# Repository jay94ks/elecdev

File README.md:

# Custom Development Board Projects.
This project is for making custom development boards with minimal circuits to power MCUs, including programming them.

## MISC
* USB-C breakout: https://github.com/jay94ks/elecdev/tree/main/misc/USB_C_BREAKOUT

## Raspberry-Pi Silicon
### RP2040
See this directory: https://github.com/jay94ks/elecdev/tree/main/rp2040 <br />
ARM® Cortex®-M0+ Dual-core, 32bit, QFN-56.<br />
Features: 133 MHz max, 256kB SRAM, `UART` x2, `SPI` x2, `I2C` x2, `PWM` x 16 channel.<br/>

### TODO: RP2350A, RP2354A 
### TODO: RP2350B, RP2354B
I'm waiting for these chips are available on chip stores. :)

## STM32
I love STMicroelectronics's `TSSOP-20` and `TSOP-8` (G03xJ6Mx).
It is small, has few pins, is easy to use by plugging it into a breadboard,
and has a simple peripheral circuit. I even like the size of the flash memory and the size of the built-in RAM. 
Additionally, they fit well on any board that can be made easily, and there is little need to configure an external clock circuit.
I hope more chips will be released in `TSSOP-20`, `TSSOP-16` or `TSOP-8` versions. And it would be better if they could have USB DP/DM pins.

### G030F6
See this directory: https://github.com/jay94ks/elecdev/tree/main/stm32/g030f6 <br />
ARM® Cortex®-M0, 32bit, TSOC-20.<br />
Features: 64 MHz MAX, 32K Flash, 8K RAM, `USART`, `SPI`,  `I2C`.<br/>
Board Size: 17.78 mm * 25.4 mm.<br />
Price: about 2,800 KRW, 2.11 USD.<br/>

### F042F6
See this directory: https://github.com/jay94ks/elecdev/tree/main/stm32/f042f6 <br />
ARM® Cortex®-M0, 32bit, TSOC-20.<br />
Features: 48 MHz MAX, 32K Flash, 6K RAM, `USART`, `SPI`, `USB FS`, `CAN`, `I2C`.<br/>
Board Size: 22.86 mm * 32.05 mm.<br />
Price: about 5,500 KRW, 4.15 USD.<br/>

### F107RBT6
See this directory: https://github.com/jay94ks/elecdev/tree/main/stm32/f107rbt6 <br />

### G030K8
See this directory: https://github.com/jay94ks/elecdev/tree/main/stm32/g030k8 <br />

## WCH
### CH32V003F4P6
See this directory: https://github.com/jay94ks/elecdev/tree/main/wch/ch32v003f4p6 <br />

### CH32V003F4U6
See this directory: https://github.com/jay94ks/elecdev/tree/main/wch/ch32v003f4u6 <br />

### CH32X033F6P6
TODO: I bought this chip few weeks ago, I'll design this one soon. (100 pcs)

### CH32X035G8U6
See this directory:  https://github.com/jay94ks/elecdev/tree/main/wch/ch32x035g8u6 <br />

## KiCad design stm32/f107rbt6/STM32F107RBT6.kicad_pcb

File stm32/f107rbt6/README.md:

## STM32F107RBT6
This custom board contains: LAN8720A, PoE support.

### Enable Ethernet on Connectivity.
Configure `Parameter Settings`(`ETH` in `Connectivity` page) like:

* Mode: `RMII`.
* Ethernet Media Configuration: as your wish.
* Ethernet MAC Address: set anything except `00:00:00:00:00:00`.
* PHY Address Value: `0` (this is important!)

And then, enable `LWIP` to test the board's ethernet operational:
(This is located at `Middleware`)
* Check `Enabled` on `LWIP`.
* `LWIP_ICMP` on `General Settings`: Enabled. <-- `ping` command is based on `ICMP` traffic.
* `MEM_SIZE` on `Key Options`: `10 * 1600`. (Optional)

### Pin Mapping.
To enable this chip functionality, configure `RMII`:

* RCC: 8MHz.
* PC1: ETH_MDC
* PA1: ETH_REF_CLK
* PA2: ETH_MDIO
* PA7: ETH_CRS_DV
* PC4: ETH_RXD0
* PC5: ETH_RXD1
* PB10: ETH_RX_ER
* PB11: ETH_TX_EN
* PB12: ETH_TXD0
* PB13: ETH_TXD1
* PA11: USB_OTG_FS_DM
* PA12: USB_OTG_FS_DP

### LAN8720A.
STM32CubeIDE supports only `LAN8742A` but, `LAN8720A` is available with few changes.
Configure `Advanced Parameters`(`ETH` in `Connectivity` page) like:

* PHY: `LAN8742A_PHY_ADDRESS`
* Transceiver Basic Control Register: `0x00`
* Transceiver Basic Status Register: `0x01`
* PHY special control/status register Offset: `0x1f`
* PHY interrupt source flag register Offset: `0x001d`
* PHY Link down interrupt: `0x0010`

When if `PHY Address Value` is not editable even though this changed on `Parameter Settings`,
This can be modified by header file: `stm32f1xx_hal_conf.h` on `Core/Inc` directory.

```
......
/* Section 2: PHY configuration section */

/* LAN8742A_PHY_ADDRESS Address*/
// #define LAN8742A_PHY_ADDRESS         0x1U    // <-- comment this.
#define LAN8742A_PHY_ADDRESS            0x0U    // <-- set `PHY_ADDRESS` here

......
```

Then, you can program the board supports `10/100 Mbps Ethernet`.

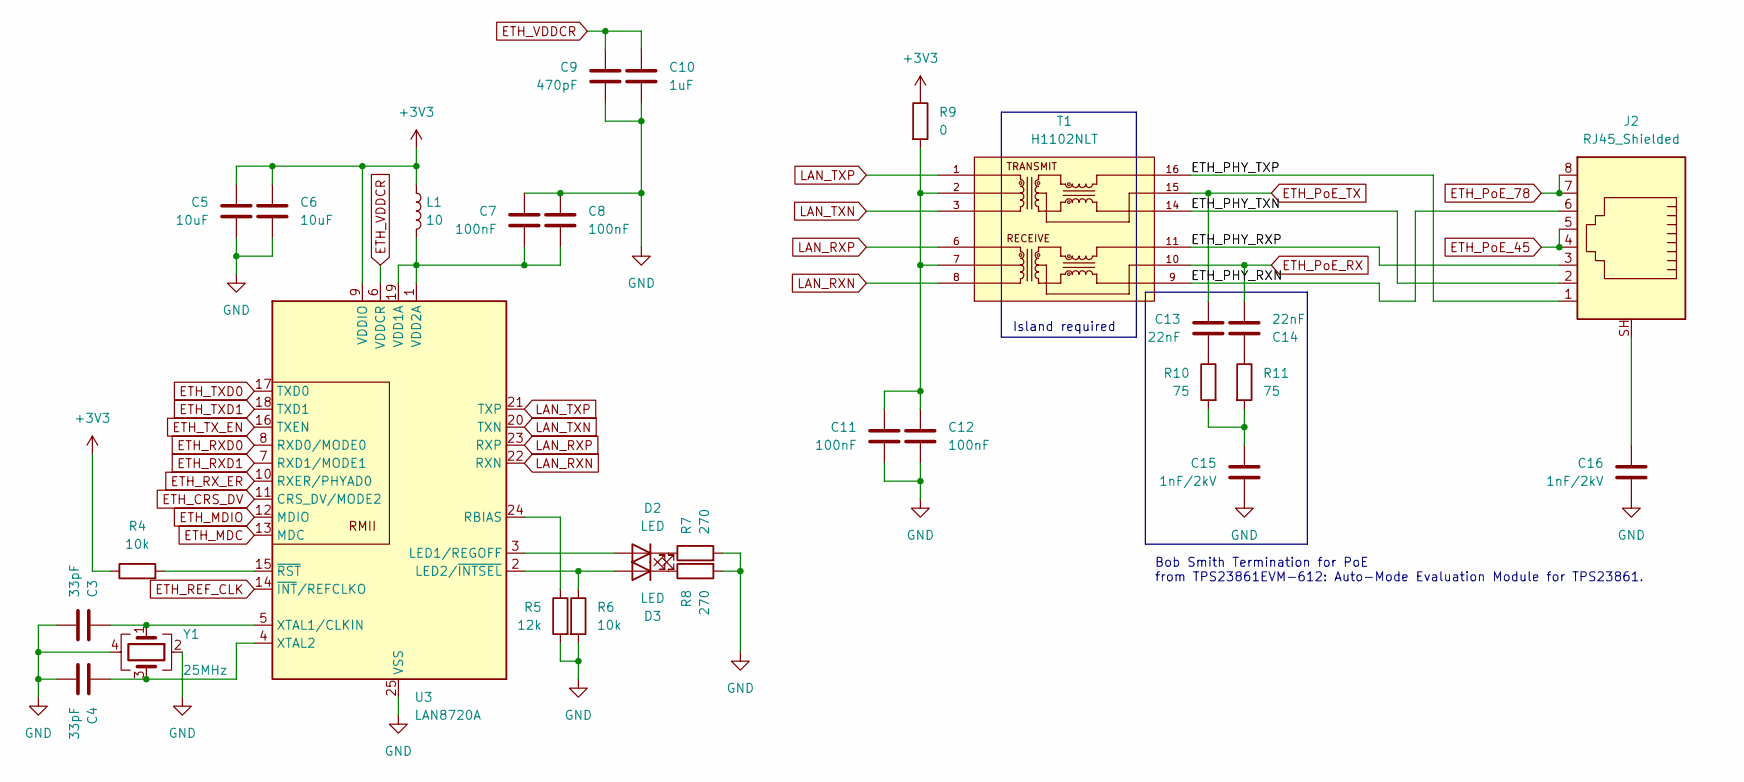
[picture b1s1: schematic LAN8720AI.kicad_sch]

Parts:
C3, C4: 33pF; C_0603_1608Metric
C5, C6: 10uF; C_0603_1608Metric
C7, C8, C11, C12: 100nF; C_0603_1608Metric
C9: 470pF; C_0603_1608Metric
C10: 1uF; C_0603_1608Metric
C13, C14: 22nF; C_0603_1608Metric
C15, C16: 1nF/2kV; C_0603_1608Metric
D2, D3: LED; LED_0603_1608Metric
J2: RJ45_Shielded; RJ45_Ninigi_GE
L1: 10; L_0603_1608Metric
R4, R6: 10k; R_0603_1608Metric
R5: 12k; R_0603_1608Metric
R7, R8: 270; R_0603_1608Metric
R9: 0; R_0603_1608Metric
R10, R11: 75; R_0603_1608Metric
T1: H1102NLT; XFMR_H1102NLT; PARTREV NA
U3: LAN8720A; VQFN-24-1EP_4x4mm_P0.5mm_EP2.45x2.45mm
Y1: 25MHz; Crystal_SMD_3225-4Pin_3.2x2.5mm

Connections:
+3V3: C5.1, C6.1, L1.1, R4.1, R9.1, U3.9 (VDDIO); also elsewhere on the board
/LAN8720AI/ETH_PHY_RXN: J2.6, T1.9
/LAN8720AI/ETH_PHY_RXP: J2.3, T1.11
/LAN8720AI/ETH_PHY_TXN: J2.2, T1.14
/LAN8720AI/ETH_PHY_TXP: J2.1, T1.16
ETH_CRS_DV: U3.11 (CRS_DV/MODE2); also elsewhere on the board
ETH_MDC: U3.13 (MDC); also elsewhere on the board
ETH_MDIO: U3.12 (MDIO); also elsewhere on the board
ETH_PoE_45: J2.4, J2.5; also elsewhere on the board
ETH_PoE_78: J2.7, J2.8; also elsewhere on the board
ETH_PoE_RX: C14.2, T1.10; also elsewhere on the board
ETH_PoE_TX: C13.1, T1.15; also elsewhere on the board
ETH_REF_CLK: U3.14 (~INT/REFCLKO); also elsewhere on the board
ETH_RXD0: U3.8 (RXD0/MODE0); also elsewhere on the board
ETH_RXD1: U3.7 (RXD1/MODE1); also elsewhere on the board
ETH_RX_ER: U3.10 (RXER/PHYAD0); also elsewhere on the board
ETH_TXD0: U3.17 (TXD0); also elsewhere on the board
ETH_TXD1: U3.18 (TXD1); also elsewhere on the board
ETH_TX_EN: U3.16 (TXEN); also elsewhere on the board
ETH_VDDCR: C9.1, C10.1, U3.6 (VDDCR)
GND: C3.2, C4.2, C5.2, C6.2, C7.1, C8.1, C9.2, C10.2, C11.2, C12.2, C15.2, C16.2, R5.2, R6.2, R7.2, R8.2, U3.25 (VSS), Y1.2, Y1.4; also elsewhere on the board
LAN_RXN: T1.8, U3.22 (RXN)
LAN_RXP: T1.6, U3.23 (RXP)
LAN_TXN: T1.3, U3.20 (TXN)
LAN_TXP: T1.1, U3.21 (TXP)
unnamed: C11.1, C12.1, R9.2, T1.2, T1.7
unnamed: C13.2, R10.1
unnamed: C14.1, R11.1
unnamed: C15.1, R10.2, R11.2
unnamed: C16.1, J2.SH
unnamed: D2.2 (A), U3.3 (LED1/REGOFF)
unnamed: D2.1 (K), R7.1
unnamed: D3.2 (A), R6.1, U3.2 (LED2/~INTSEL)
unnamed: D3.1 (K), R8.1
unnamed: R5.1, U3.24 (RBIAS)
unnamed: C7.2, C8.2, L1.2, U3.1 (VDD2A), U3.19 (VDD1A)
unnamed: C3.1, U3.5 (XTAL1/CLKIN), Y1.1
unnamed: C4.1, U3.4 (XTAL2), Y1.3
unnamed: R4.2, U3.15 (~RST)

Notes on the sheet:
Bob Smith Termination for PoE from TPS23861EVM-612: Auto-Mode Evaluation Module for TPS23861.
Island required

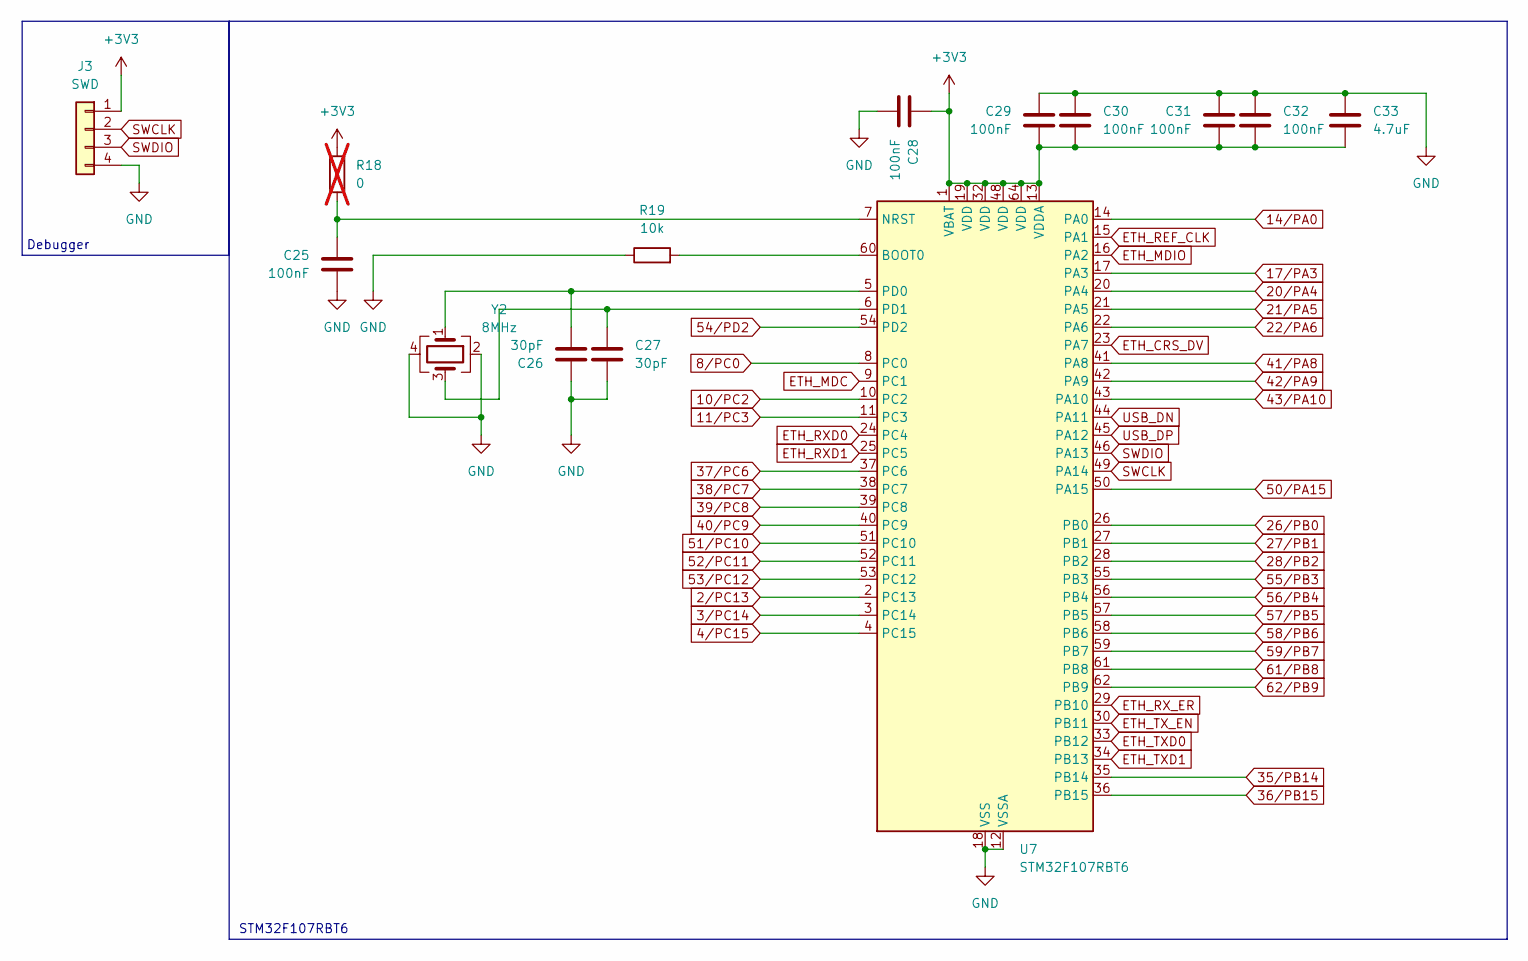
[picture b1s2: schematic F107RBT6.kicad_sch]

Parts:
C25, C28, C29, C30, C31, C32: 100nF; C_0603_1608Metric
C26, C27: 30pF; C_0603_1608Metric
C33: 4.7uF; C_0603_1608Metric
J3: SWD; PinHeader_1x04_P2.54mm_Vertical
R18: 0; R_0603_1608Metric; not fitted
R19: 10k; R_0603_1608Metric
U7: STM32F107RBT6; LQFP-64_10x10mm_P0.5mm
Y2: 8MHz; Crystal_SMD_3225-4Pin_3.2x2.5mm

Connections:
2/PC13: U7.2 (PC13); also elsewhere on the board
3/PC14: U7.3 (PC14); also elsewhere on the board
4/PC15: U7.4 (PC15); also elsewhere on the board
8/PC0: U7.8 (PC0); also elsewhere on the board
10/PC2: U7.10 (PC2); also elsewhere on the board
11/PC3: U7.11 (PC3); also elsewhere on the board
14/PA0: U7.14 (PA0); also elsewhere on the board
17/PA3: U7.17 (PA3); also elsewhere on the board
20/PA4: U7.20 (PA4); also elsewhere on the board
21/PA5: U7.21 (PA5); also elsewhere on the board
22/PA6: U7.22 (PA6); also elsewhere on the board
26/PB0: U7.26 (PB0); also elsewhere on the board
27/PB1: U7.27 (PB1); also elsewhere on the board
28/PB2: U7.28 (PB2); also elsewhere on the board
35/PB14: U7.35 (PB14); also elsewhere on the board
36/PB15: U7.36 (PB15); also elsewhere on the board
37/PC6: U7.37 (PC6); also elsewhere on the board
38/PC7: U7.38 (PC7); also elsewhere on the board
39/PC8: U7.39 (PC8); also elsewhere on the board
40/PC9: U7.40 (PC9); also elsewhere on the board
41/PA8: U7.41 (PA8); also elsewhere on the board
42/PA9: U7.42 (PA9); also elsewhere on the board
43/PA10: U7.43 (PA10); also elsewhere on the board
50/PA15: U7.50 (PA15); also elsewhere on the board
51/PC10: U7.51 (PC10); also elsewhere on the board
52/PC11: U7.52 (PC11); also elsewhere on the board
53/PC12: U7.53 (PC12); also elsewhere on the board
54/PD2: U7.54 (PD2); also elsewhere on the board
55/PB3: U7.55 (PB3); also elsewhere on the board
56/PB4: U7.56 (PB4); also elsewhere on the board
57/PB5: U7.57 (PB5); also elsewhere on the board
58/PB6: U7.58 (PB6); also elsewhere on the board
59/PB7: U7.59 (PB7); also elsewhere on the board
61/PB8: U7.61 (PB8); also elsewhere on the board
62/PB9: U7.62 (PB9); also elsewhere on the board
+3V3: C28.1, C29.2, C30.2, C31.2, C32.2, C33.2, J3.1, R18.1, U7.1 (VBAT), U7.13 (VDDA), U7.19 (VDD), U7.32 (VDD), U7.48 (VDD), U7.64 (VDD); also elsewhere on the board
ETH_CRS_DV: U7.23 (PA7); also elsewhere on the board
ETH_MDC: U7.9 (PC1); also elsewhere on the board
ETH_MDIO: U7.16 (PA2); also elsewhere on the board
ETH_REF_CLK: U7.15 (PA1); also elsewhere on the board
ETH_RXD0: U7.24 (PC4); also elsewhere on the board
ETH_RXD1: U7.25 (PC5); also elsewhere on the board
ETH_RX_ER: U7.29 (PB10); also elsewhere on the board
ETH_TXD0: U7.33 (PB12); also elsewhere on the board
ETH_TXD1: U7.34 (PB13); also elsewhere on the board
ETH_TX_EN: U7.30 (PB11); also elsewhere on the board
GND: C25.2, C26.1, C27.2, C28.2, C29.1, C30.1, C31.1, C32.1, C33.1, J3.4, R19.1, U7.12 (VSSA), U7.18 (VSS), U7.31 (VSS), U7.47 (VSS), U7.63 (VSS), Y2.2, Y2.4; also elsewhere on the board
unnamed: R19.2, U7.60 (BOOT0)
unnamed: C25.1, R18.2, U7.7 (NRST)
unnamed: C26.2, U7.5 (PD0), Y2.1
unnamed: C27.1, U7.6 (PD1), Y2.3
SWCLK: J3.2, U7.49 (PA14)
SWDIO: J3.3, U7.46 (PA13)
USB_DN: U7.44 (PA11); also elsewhere on the board
USB_DP: U7.45 (PA12); also elsewhere on the board

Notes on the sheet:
STM32F107RBT6
Debugger

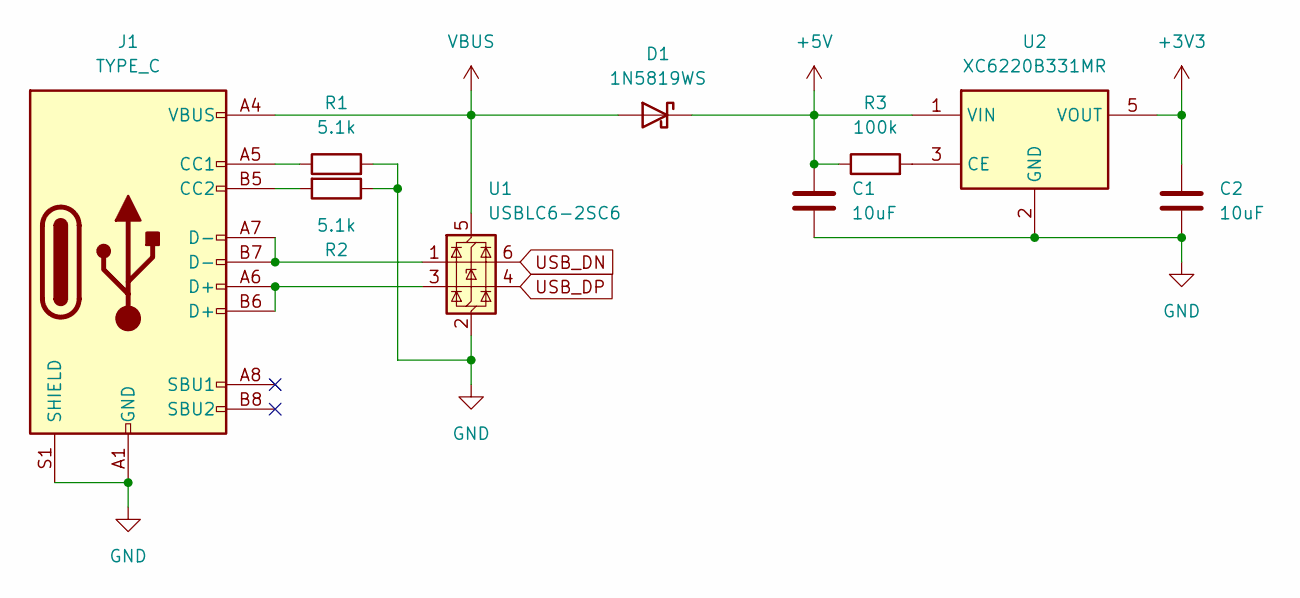
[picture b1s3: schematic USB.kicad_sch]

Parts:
C1, C2: 10uF; C_0603_1608Metric
D1: 1N5819WS; D_SOD-323
J1: TYPE_C; USB_C_Receptacle_Palconn_UTC16-G
R1, R2: 5.1k; R_0603_1608Metric
R3: 100k; R_0603_1608Metric
U1: USBLC6-2SC6; SOT-23-6
U2: XC6220B331MR; SOT-23-5

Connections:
+3V3: C2.1, U2.5 (VOUT); also elsewhere on the board
+5V: C1.1, D1.1 (K), R3.1, U2.1 (VIN); also elsewhere on the board
GND: C1.2, C2.2, J1.A1 (GND), J1.A12 (GND), J1.B1 (GND), J1.B12 (GND), J1.S1 (SHIELD), R1.2, R2.1, U1.2 (GND), U2.2 (GND); also elsewhere on the board
unnamed: J1.A5 (CC1), R1.1
unnamed: J1.B5 (CC2), R2.2
unnamed: J1.A6 (D+), J1.B6 (D+), U1.3 (I/O2)
unnamed: J1.A7 (D-), J1.B7 (D-), U1.1 (I/O1)
unnamed: R3.2, U2.3 (CE)
USB_DN: U1.6 (I/O1); also elsewhere on the board
USB_DP: U1.4 (I/O2); also elsewhere on the board
VBUS: D1.2 (A), J1.A4 (VBUS), J1.A9 (VBUS), J1.B4 (VBUS), J1.B9 (VBUS), U1.5 (VBUS)

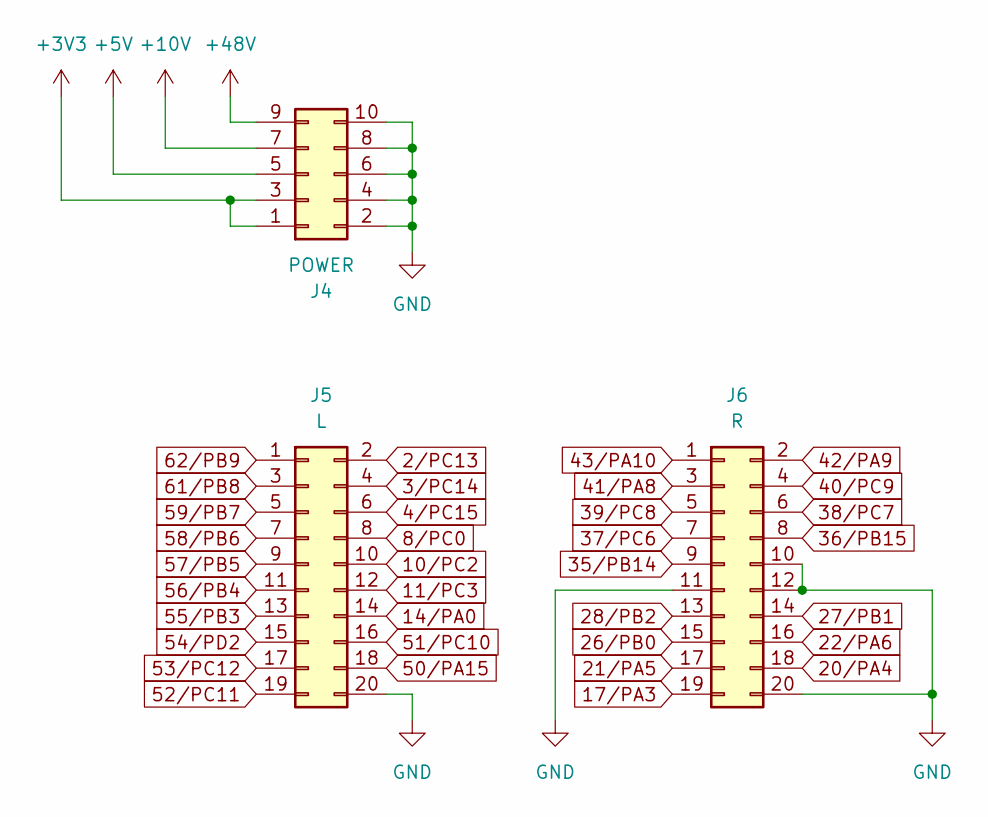
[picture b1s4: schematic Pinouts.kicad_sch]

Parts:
J4: POWER; PinHeader_2x05_P2.54mm_Vertical
J5: L; PinHeader_2x10_P2.54mm_Vertical
J6: R; PinHeader_2x10_P2.54mm_Vertical

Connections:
2/PC13: J5.2; also elsewhere on the board
3/PC14: J5.4; also elsewhere on the board
4/PC15: J5.6; also elsewhere on the board
8/PC0: J5.8; also elsewhere on the board
10/PC2: J5.10; also elsewhere on the board
11/PC3: J5.12; also elsewhere on the board
14/PA0: J5.14; also elsewhere on the board
17/PA3: J6.19; also elsewhere on the board
20/PA4: J6.18; also elsewhere on the board
21/PA5: J6.17; also elsewhere on the board
22/PA6: J6.16; also elsewhere on the board
26/PB0: J6.15; also elsewhere on the board
27/PB1: J6.14; also elsewhere on the board
28/PB2: J6.13; also elsewhere on the board
35/PB14: J6.9; also elsewhere on the board
36/PB15: J6.8; also elsewhere on the board
37/PC6: J6.7; also elsewhere on the board
38/PC7: J6.6; also elsewhere on the board
39/PC8: J6.5; also elsewhere on the board
40/PC9: J6.4; also elsewhere on the board
41/PA8: J6.3; also elsewhere on the board
42/PA9: J6.2; also elsewhere on the board
43/PA10: J6.1; also elsewhere on the board
50/PA15: J5.18; also elsewhere on the board
51/PC10: J5.16; also elsewhere on the board
52/PC11: J5.19; also elsewhere on the board
53/PC12: J5.17; also elsewhere on the board
54/PD2: J5.15; also elsewhere on the board
55/PB3: J5.13; also elsewhere on the board
56/PB4: J5.11; also elsewhere on the board
57/PB5: J5.9; also elsewhere on the board
58/PB6: J5.7; also elsewhere on the board
59/PB7: J5.5; also elsewhere on the board
61/PB8: J5.3; also elsewhere on the board
62/PB9: J5.1; also elsewhere on the board
+3V3: J4.1, J4.3; also elsewhere on the board
+5V: J4.5; also elsewhere on the board
+10V: J4.7; also elsewhere on the board
+48V: J4.9; also elsewhere on the board
GND: J4.2, J4.4, J4.6, J4.8, J4.10, J5.20, J6.10, J6.11, J6.12, J6.20; also elsewhere on the board

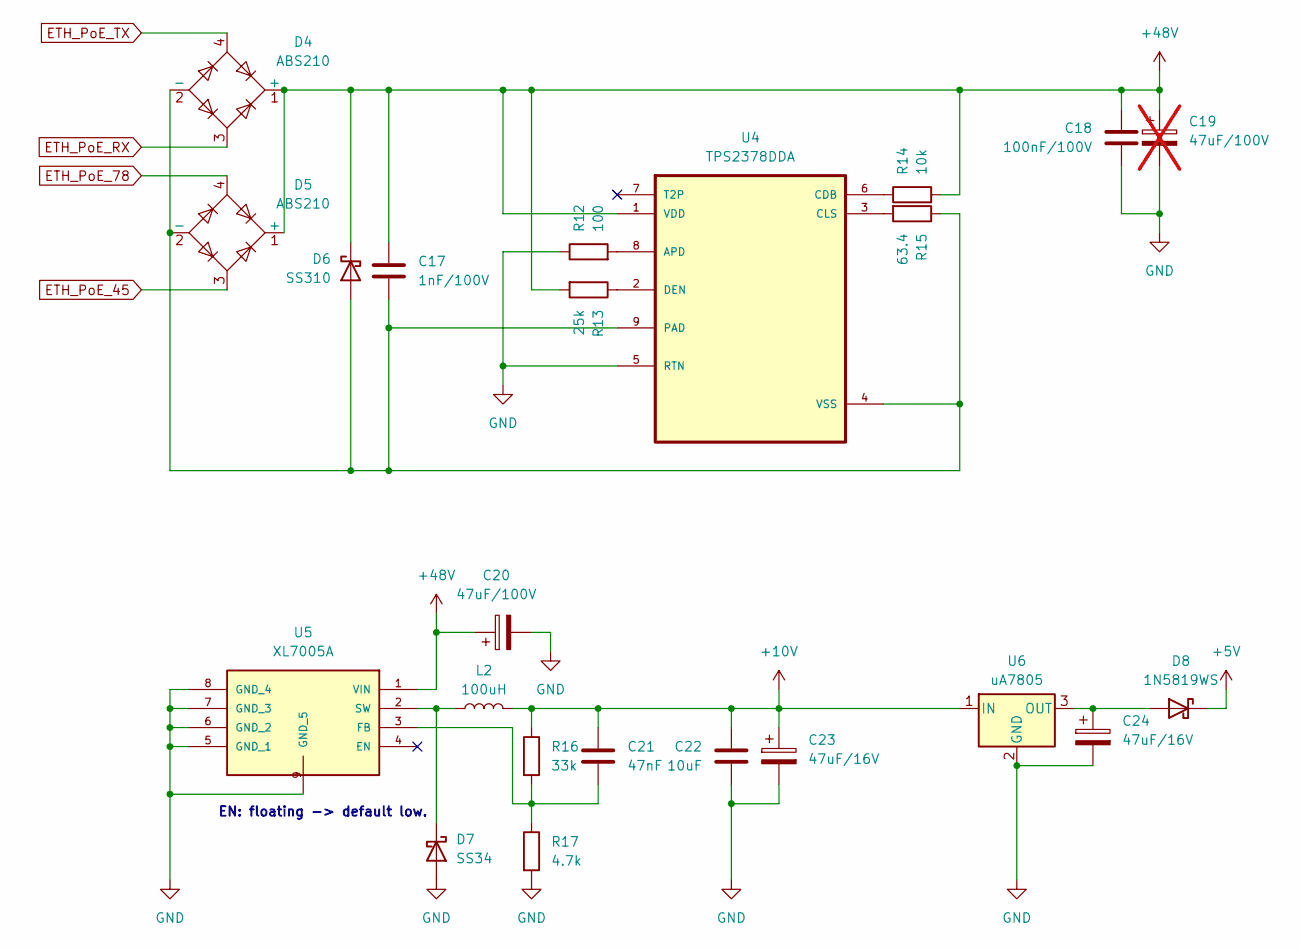
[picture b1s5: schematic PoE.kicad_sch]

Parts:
C17: 1nF/100V; C_0603_1608Metric
C18: 100nF/100V; C_0603_1608Metric
C19: 47uF/100V; CP_Elec_8x10.5; not fitted
C20: 47uF/100V; CP_Elec_8x10.5
C21: 47nF; C_0603_1608Metric
C22: 10uF; C_0603_1608Metric
C23, C24: 47uF/16V; CP_Elec_5x5.4
D4, D5: ABS210; Diode_Bridge_Diotec_ABS
D6: SS310; D_SMA
D7: SS34; D_SMA
D8: 1N5819WS; D_SOD-323
L2: 100uH; L_CD32
R12: 100; R_0603_1608Metric
R13: 25k; R_0603_1608Metric
R14: 10k; R_0603_1608Metric
R15: 63.4; R_0603_1608Metric
R16: 33k; R_0603_1608Metric
R17: 4.7k; R_0603_1608Metric
U4: TPS2378DDA; HSOP-8-1EP_3.9x4.9mm_P1.27mm_EP2.41x3.1mm
U5: XL7005A; HSOP-8-1EP_3.9x4.9mm_P1.27mm_EP2.3x2.3mm; Manufacturer_Part_Number XL7005A
U6: uA7805; TO-252-2

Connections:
+5V: D8.1 (K); also elsewhere on the board
+10V: C21.1, C22.1, C23.1, L2.2, R16.1, U6.1 (IN); also elsewhere on the board
+48V: C17.1, C18.1, C19.1, C20.1, D4.1 (+), D5.1 (+), D6.1 (K), R13.2, R14.2, U4.1 (VDD), U5.1 (VIN); also elsewhere on the board
ETH_PoE_45: D5.3; also elsewhere on the board
ETH_PoE_78: D5.4; also elsewhere on the board
ETH_PoE_RX: D4.3; also elsewhere on the board
ETH_PoE_TX: D4.4; also elsewhere on the board
GND: C18.2, C19.2, C20.2, C22.2, C23.2, C24.2, D7.2 (A), R12.1, R17.2, U4.5 (RTN), U5.5 (GND_1), U5.6 (GND_2), U5.7 (GND_3), U5.8 (GND_4), U5.9 (GND_5), U6.2 (GND); also elsewhere on the board
unnamed: C17.2, D4.2 (-), D5.2 (-), D6.2 (A), R15.1, U4.4 (VSS), U4.9 (PAD)
unnamed: D7.1 (K), L2.1, U5.2 (SW)
unnamed: C24.1, D8.2 (A), U6.3 (OUT)
unnamed: R12.2, U4.8 (APD)
unnamed: R14.1, U4.6 (CDB)
unnamed: R15.2, U4.3 (CLS)
unnamed: R13.1, U4.2 (DEN)
unnamed: C21.2, R16.2, R17.1, U5.3 (FB)

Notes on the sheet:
EN: floating -> default low.

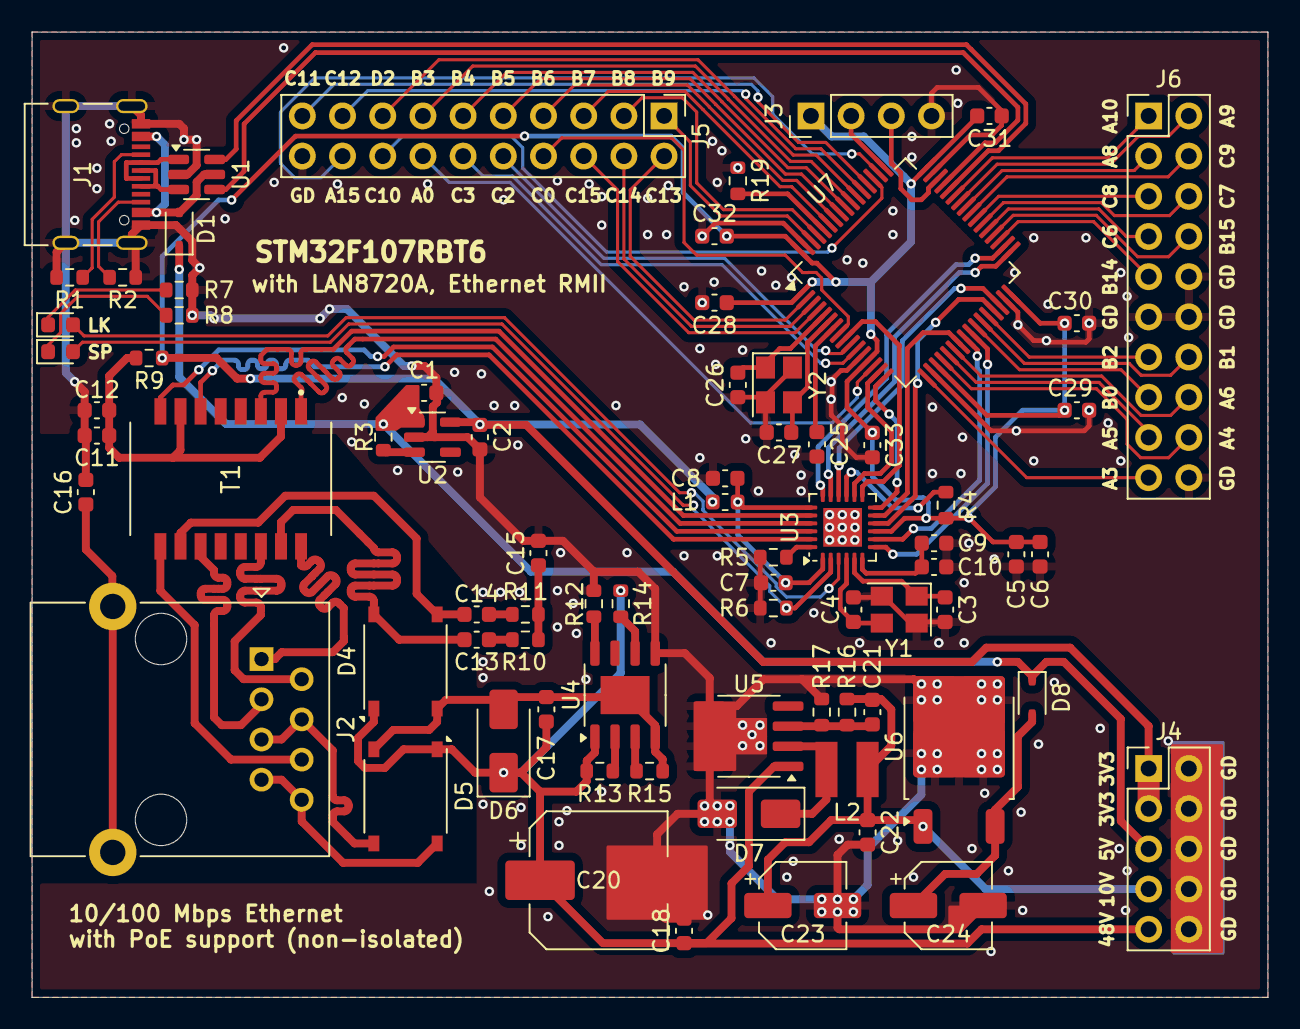
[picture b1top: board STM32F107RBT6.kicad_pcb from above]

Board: 2 copper layers, 78.1 x 61.0 mm, 76 parts (0 on the bottom side), 99 nets.

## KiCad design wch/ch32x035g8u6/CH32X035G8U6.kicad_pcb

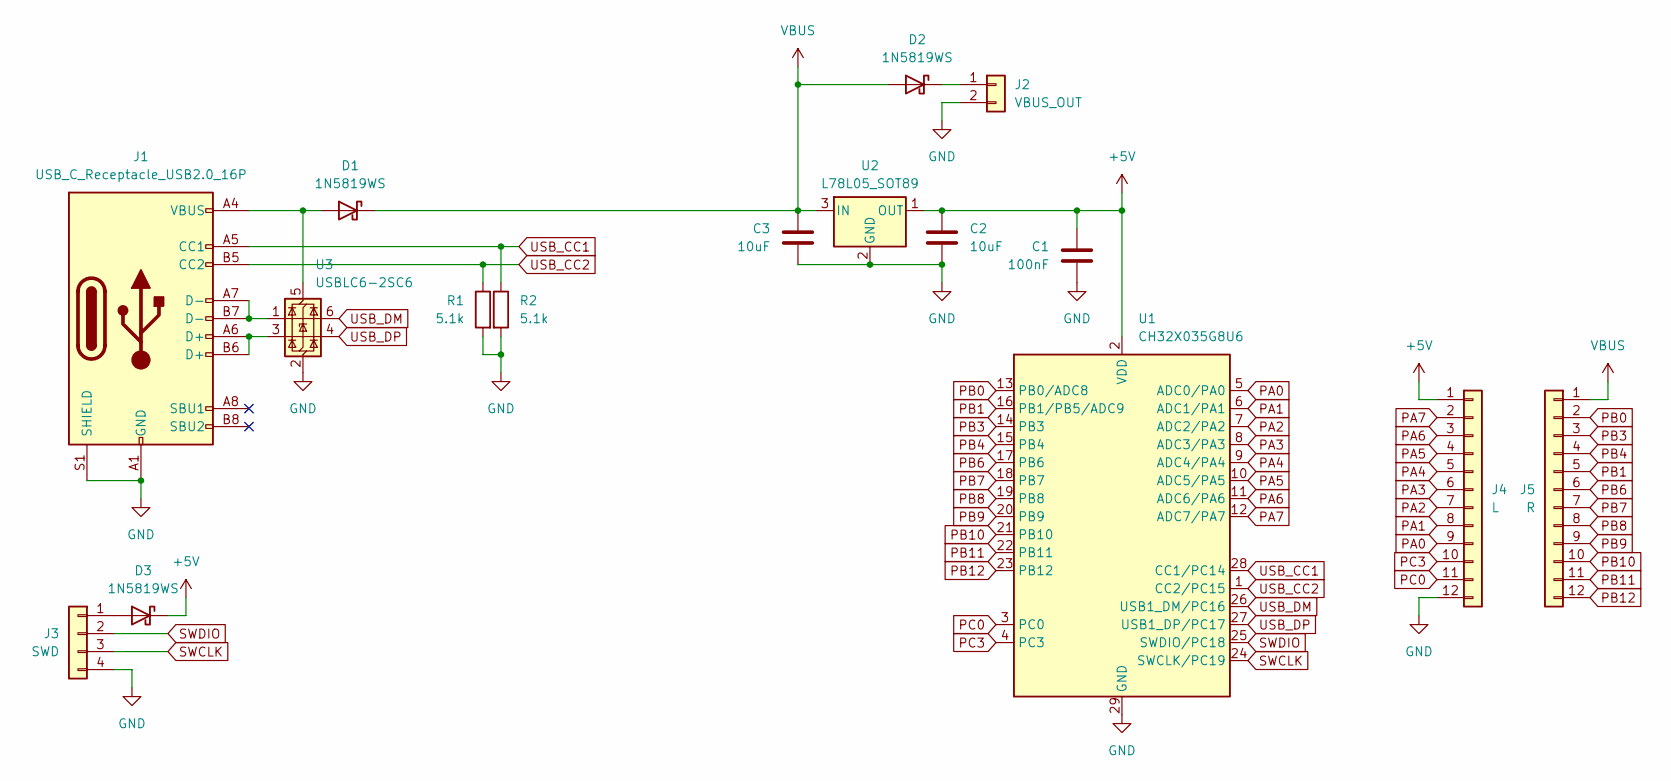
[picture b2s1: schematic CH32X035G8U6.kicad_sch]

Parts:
C1: 100nF; C_0603_1608Metric
C2, C3: 10uF; C_0603_1608Metric
D1, D2, D3: 1N5819WS; D_SOD-323_HandSoldering
J1: USB_C_Receptacle_USB2.0_16P; USB_C_Receptacle_Palconn_UTC16-G
J2: VBUS_OUT; TerminalBlock_bornier-2_P5.08mm
J3: SWD; PinHeader_1x04_P2.54mm_Vertical
J4: L; PinHeader_1x12_P2.54mm_Vertical
J5: R; PinHeader_1x12_P2.54mm_Vertical
R1, R2: 5.1k; R_0603_1608Metric
U1: CH32X035G8U6; QFN-28-1EP_4x4mm_P0.4mm_EP2.6x2.6mm
U2: L78L05_SOT89; SOT-89-3
U3: USBLC6-2SC6; SOT-23-6

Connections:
+5V: C1.1, C2.1, D3.1 (K), J4.1, U1.2 (VDD), U2.1 (OUT)
GND: C1.2, C2.2, C3.2, J1.A1 (GND), J1.A12 (GND), J1.B1 (GND), J1.B12 (GND), J1.S1 (SHIELD), J2.2, J3.4, J4.12, R1.2, R2.2, U1.29 (GND), U2.2 (GND), U3.2 (GND)
unnamed: D1.2 (A), J1.A4 (VBUS), J1.A9 (VBUS), J1.B4 (VBUS), J1.B9 (VBUS), U3.5 (VBUS)
unnamed: D2.1 (K), J2.1
unnamed: D3.2 (A), J3.1
unnamed: J1.A6 (D+), J1.B6 (D+), U3.3 (I/O2)
unnamed: J1.A7 (D-), J1.B7 (D-), U3.1 (I/O1)
PA0: J4.9, U1.5 (ADC0/PA0)
PA1: J4.8, U1.6 (ADC1/PA1)
PA2: J4.7, U1.7 (ADC2/PA2)
PA3: J4.6, U1.8 (ADC3/PA3)
PA4: J4.5, U1.9 (ADC4/PA4)
PA5: J4.4, U1.10 (ADC5/PA5)
PA6: J4.3, U1.11 (ADC6/PA6)
PA7: J4.2, U1.12 (ADC7/PA7)
PB0: J5.2, U1.13 (PB0/ADC8)
PB1: J5.5, U1.16 (PB1/PB5/ADC9)
PB3: J5.3, U1.14 (PB3)
PB4: J5.4, U1.15 (PB4)
PB6: J5.6, U1.17 (PB6)
PB7: J5.7, U1.18 (PB7)
PB8: J5.8, U1.19 (PB8)
PB9: J5.9, U1.20 (PB9)
PB10: J5.10, U1.21 (PB10)
PB11: J5.11, U1.22 (PB11)
PB12: J5.12, U1.23 (PB12)
PC0: J4.11, U1.3 (PC0)
PC3: J4.10, U1.4 (PC3)
SWCLK: J3.3, U1.24 (SWCLK/PC19)
SWDIO: J3.2, U1.25 (SWDIO/PC18)
USB_CC1: J1.A5 (CC1), R2.1, U1.28 (CC1/PC14)
USB_CC2: J1.B5 (CC2), R1.1, U1.1 (CC2/PC15)
USB_DM: U1.26 (USB1_DM/PC16), U3.6 (I/O1)
USB_DP: U1.27 (USB1_DP/PC17), U3.4 (I/O2)
VBUS: C3.1, D1.1 (K), D2.2 (A), J5.1, U2.3 (IN)

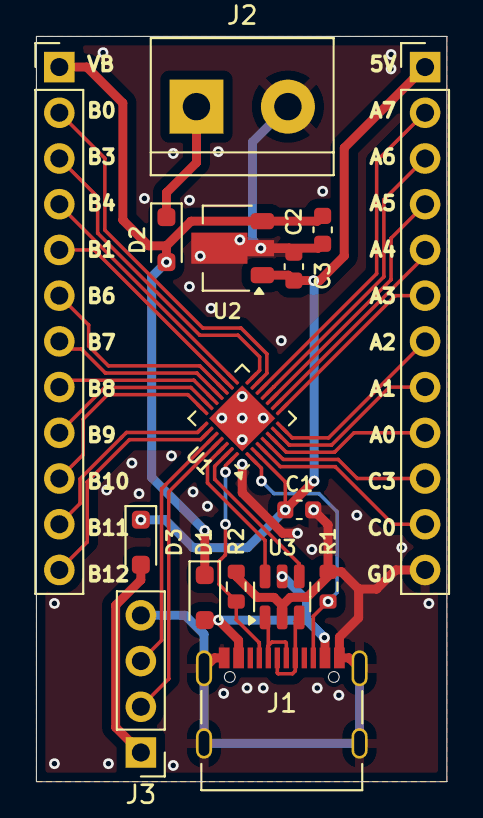
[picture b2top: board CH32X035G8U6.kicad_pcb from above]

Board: 2 copper layers, 22.8 x 41.4 mm, 16 parts (0 on the bottom side), 35 nets.

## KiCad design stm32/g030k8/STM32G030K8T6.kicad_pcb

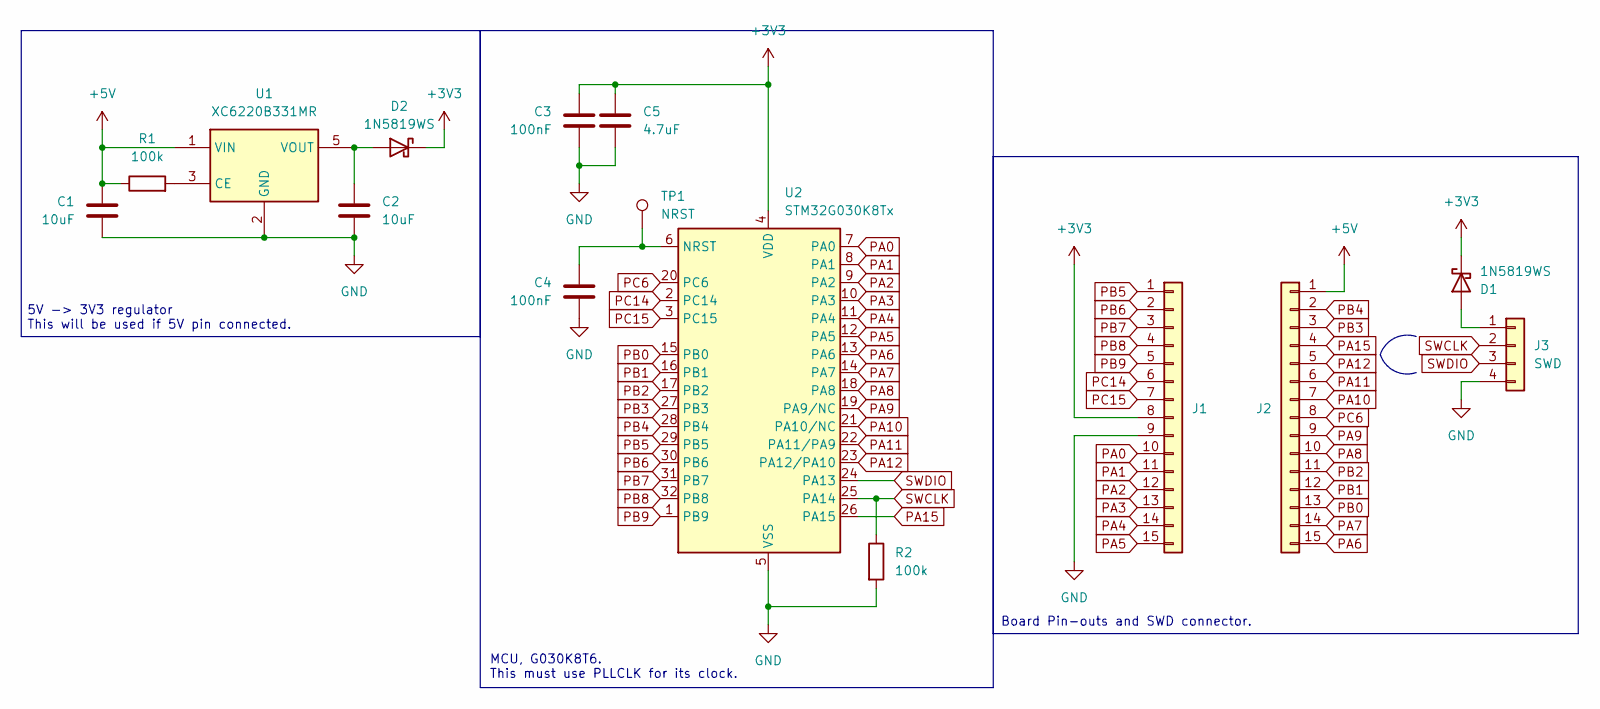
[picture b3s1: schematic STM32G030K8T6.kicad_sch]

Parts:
C1, C2: 10uF; C_0603_1608Metric
C3, C4: 100nF; C_0603_1608Metric
C5: 4.7uF; C_0603_1608Metric
D1, D2: 1N5819WS; D_SOD-323_HandSoldering
J1, J2: Conn_01x15; PinHeader_1x15_P2.54mm_Vertical
J3: SWD; PinHeader_1x04_P2.54mm_Horizontal
R1, R2: 100k; R_0603_1608Metric
TP1: NRST; TestPoint_Pad_D1.0mm
U1: XC6220B331MR; SOT-23-5
U2: STM32G030K8Tx; LQFP-32_7x7mm_P0.8mm

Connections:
+3V3: C3.1, C5.1, D1.1 (K), D2.1 (K), J1.8, U2.4 (VDD)
+5V: C1.1, J2.1, R1.1, U1.1 (VIN)
GND: C1.2, C2.2, C3.2, C4.2, C5.2, J1.9, J3.4, R2.2, U1.2 (GND), U2.5 (VSS)
unnamed: D1.2 (A), J3.1
unnamed: C2.1, D2.2 (A), U1.5 (VOUT)
unnamed: R1.2, U1.3 (CE)
unnamed: C4.1, TP1.1, U2.6 (NRST)
PA0: J1.10, U2.7 (PA0)
PA1: J1.11, U2.8 (PA1)
PA2: J1.12, U2.9 (PA2)
PA3: J1.13, U2.10 (PA3)
PA4: J1.14, U2.11 (PA4)
PA5: J1.15, U2.12 (PA5)
PA6: J2.15, U2.13 (PA6)
PA7: J2.14, U2.14 (PA7)
PA8: J2.10, U2.18 (PA8)
PA9: J2.9, U2.19 (PA9/NC)
PA10: J2.7, U2.21 (PA10/NC)
PA11: J2.6, U2.22 (PA11/PA9)
PA12: J2.5, U2.23 (PA12/PA10)
PA15: J2.4, U2.26 (PA15)
PB0: J2.13, U2.15 (PB0)
PB1: J2.12, U2.16 (PB1)
PB2: J2.11, U2.17 (PB2)
PB3: J2.3, U2.27 (PB3)
PB4: J2.2, U2.28 (PB4)
PB5: J1.1, U2.29 (PB5)
PB6: J1.2, U2.30 (PB6)
PB7: J1.3, U2.31 (PB7)
PB8: J1.4, U2.32 (PB8)
PB9: J1.5, U2.1 (PB9)
PC6: J2.8, U2.20 (PC6)
PC14: J1.6, U2.2 (PC14)
PC15: J1.7, U2.3 (PC15)
SWCLK: J3.2, R2.1, U2.25 (PA14)
SWDIO: J3.3, U2.24 (PA13)

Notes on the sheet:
5V -> 3V3 regulator This will be used if 5V pin connected.
Board Pin-outs and SWD connector.
MCU, G030K8T6. This must use PLLCLK for its clock.

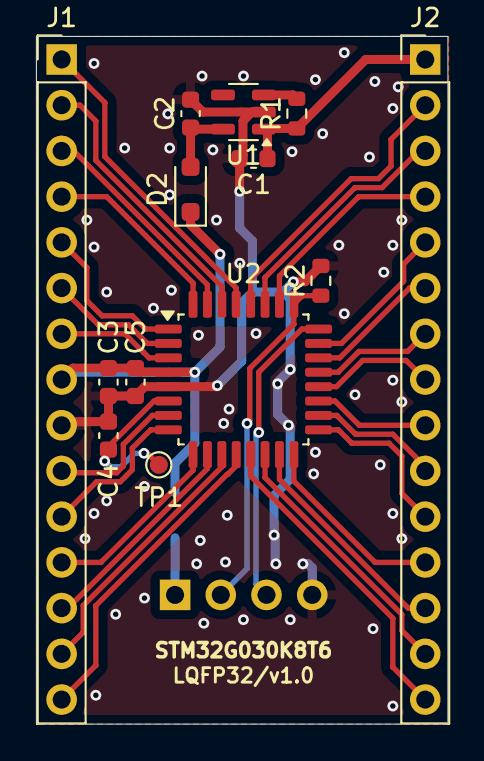
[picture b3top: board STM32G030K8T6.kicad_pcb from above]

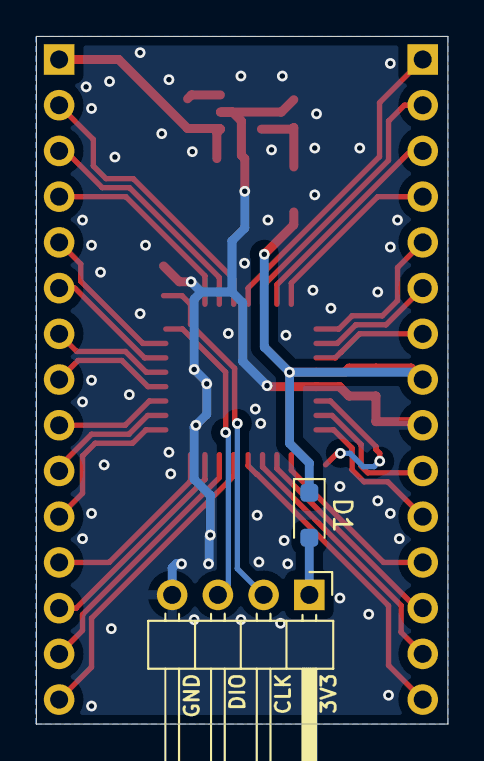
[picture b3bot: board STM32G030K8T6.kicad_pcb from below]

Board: 2 copper layers, 22.9 x 38.2 mm, 15 parts (2 on the bottom side), 36 nets.

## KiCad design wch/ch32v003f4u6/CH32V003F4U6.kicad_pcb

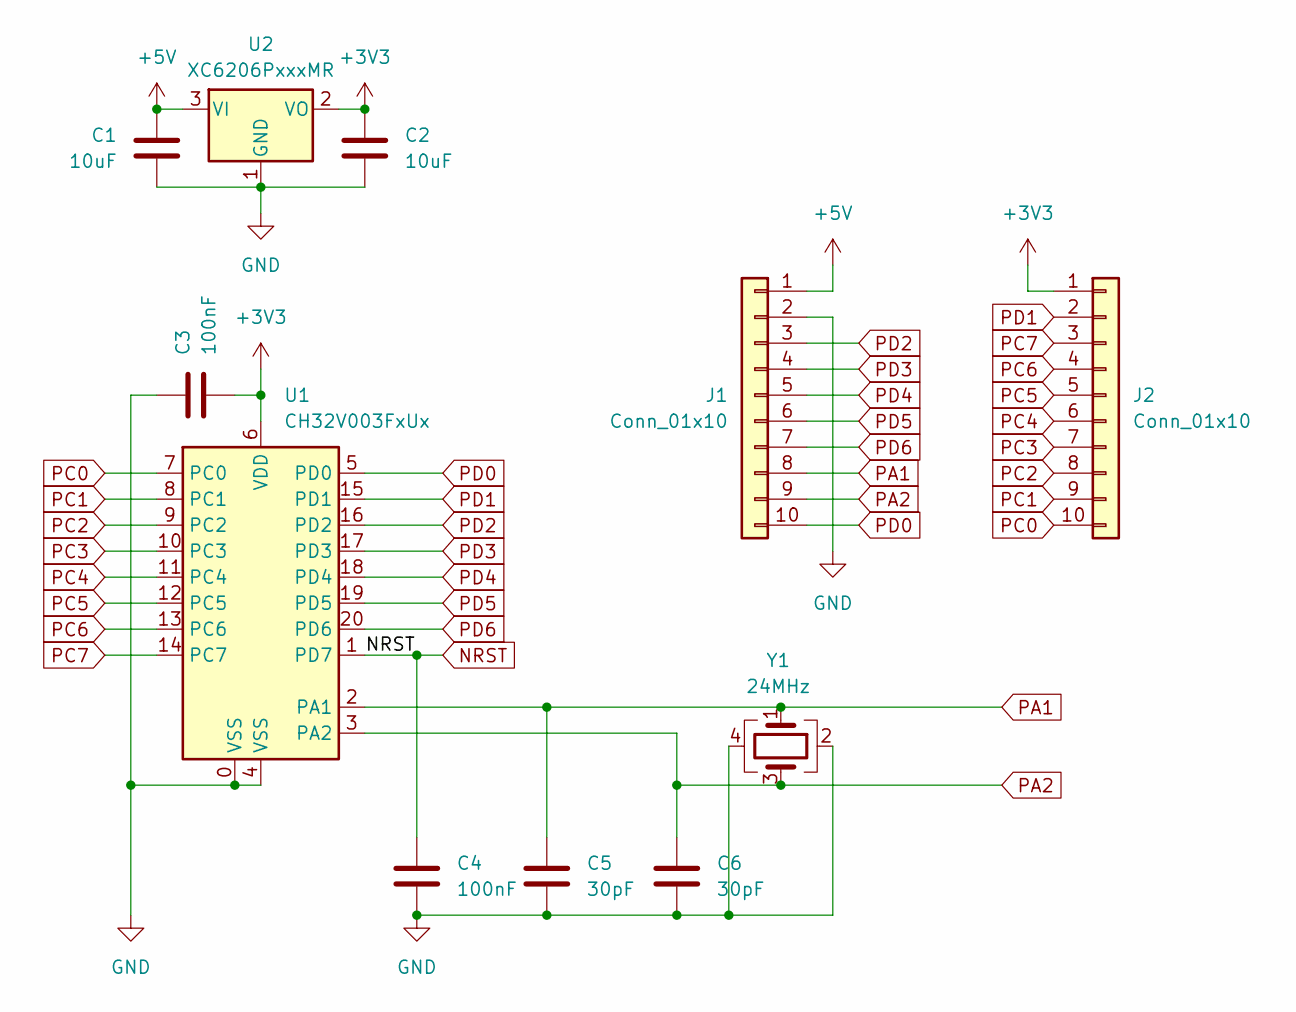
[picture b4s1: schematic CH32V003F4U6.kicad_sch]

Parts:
C1, C2: 10uF; C_0603_1608Metric
C3, C4: 100nF; C_0603_1608Metric
C5, C6: 30pF; C_0603_1608Metric
J1, J2: Conn_01x10; PinHeader_1x10_P2.54mm_Vertical
U1: CH32V003FxUx; QFN-20-1EP_3x3mm_P0.4mm_EP1.65x1.65mm
U2: XC6206PxxxMR; SOT-23-3
Y1: 24MHz; Crystal_SMD_3225-4Pin_3.2x2.5mm

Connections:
+3V3: C2.1, C3.2, J2.1, U1.6 (VDD), U2.2 (VO)
+5V: C1.1, J1.1, U2.3 (VI)
GND: C1.2, C2.2, C3.1, C4.2, C5.2, C6.2, J1.2, U1.0 (VSS), U1.4 (VSS), U2.1 (GND), Y1.2, Y1.4
NRST: C4.1, U1.1 (PD7)
PA1: C5.1, J1.8, U1.2 (PA1), Y1.1
PA2: C6.1, J1.9, U1.3 (PA2), Y1.3
PC0: J2.10, U1.7 (PC0)
PC1: J2.9, U1.8 (PC1)
PC2: J2.8, U1.9 (PC2)
PC3: J2.7, U1.10 (PC3)
PC4: J2.6, U1.11 (PC4)
PC5: J2.5, U1.12 (PC5)
PC6: J2.4, U1.13 (PC6)
PC7: J2.3, U1.14 (PC7)
PD0: J1.10, U1.5 (PD0)
PD1: J2.2, U1.15 (PD1)
PD2: J1.3, U1.16 (PD2)
PD3: J1.4, U1.17 (PD3)
PD4: J1.5, U1.18 (PD4)
PD5: J1.6, U1.19 (PD5)
PD6: J1.7, U1.20 (PD6)

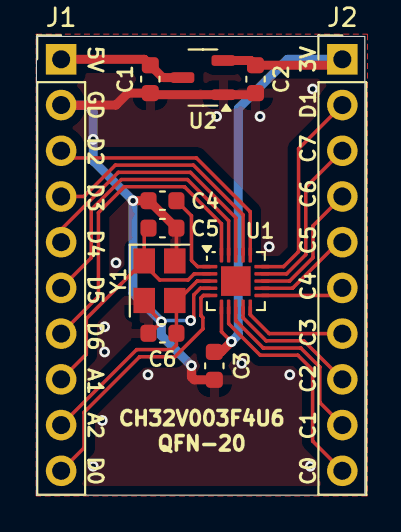
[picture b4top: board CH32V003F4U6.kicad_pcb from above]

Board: 2 copper layers, 18.2 x 25.5 mm, 11 parts (0 on the bottom side), 21 nets.
